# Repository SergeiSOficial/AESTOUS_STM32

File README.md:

# AiHi
Opensource thermostat for microbial bacteria incubator

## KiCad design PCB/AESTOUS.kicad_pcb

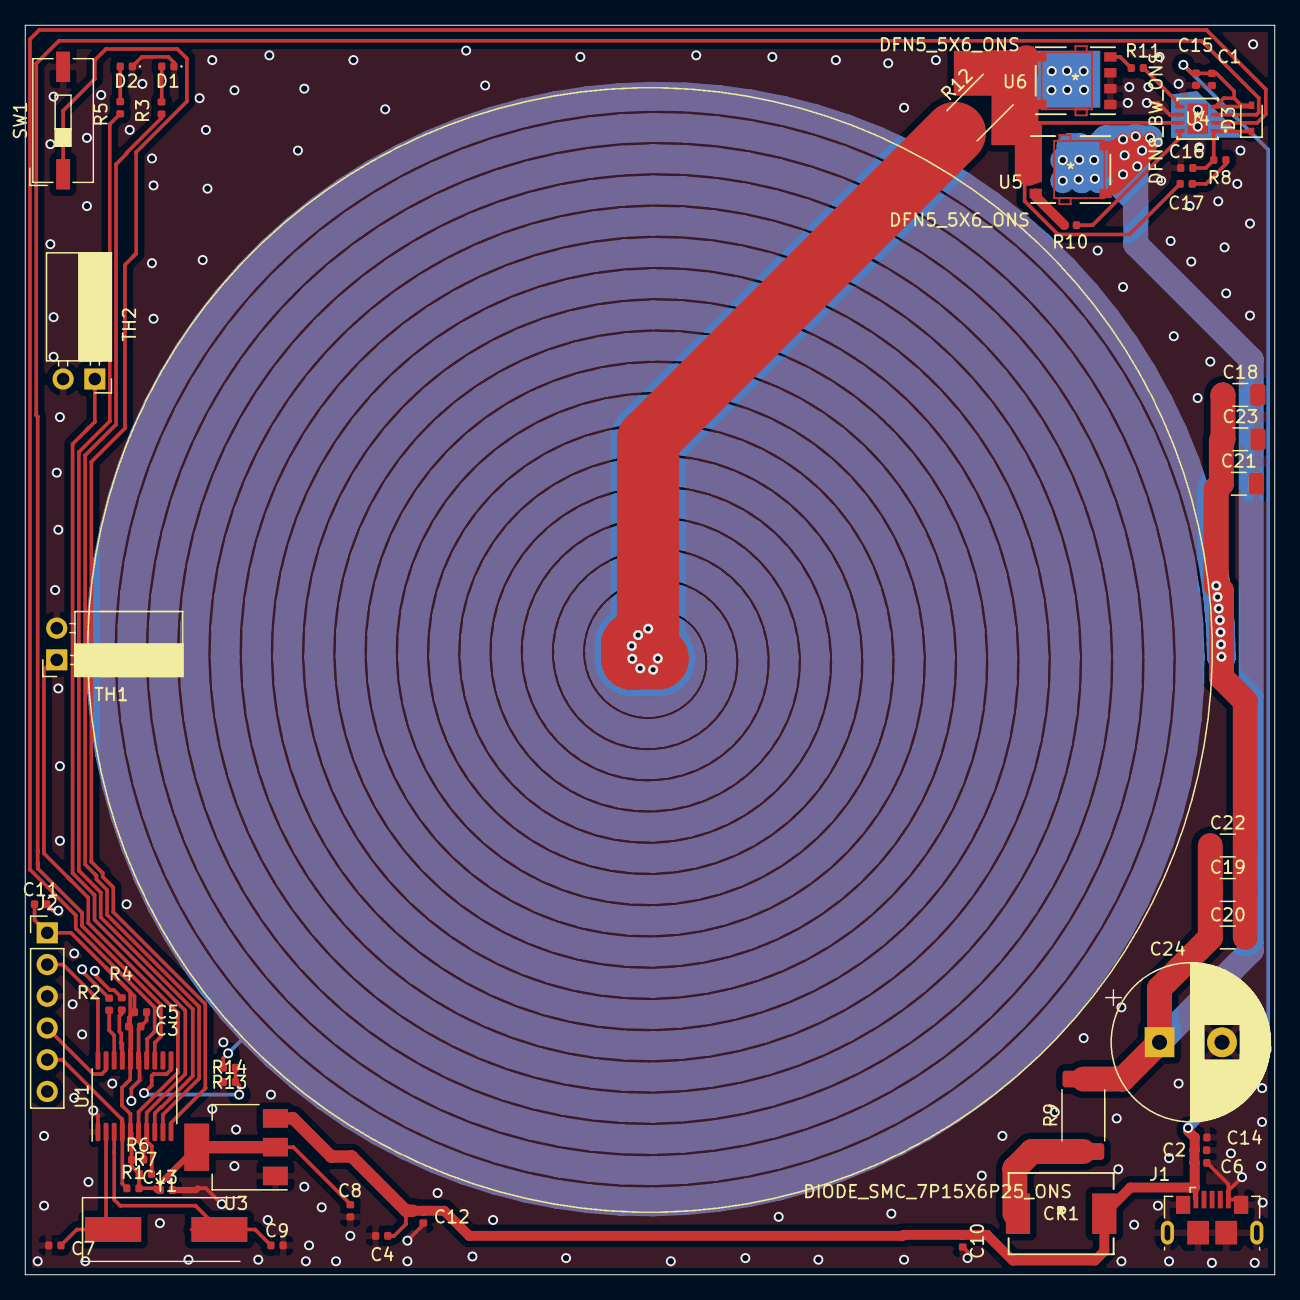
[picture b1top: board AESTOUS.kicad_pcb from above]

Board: 2 copper layers, 100.0 x 100.0 mm, 53 parts (0 on the bottom side), 32 nets.

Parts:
C1, C2, C3, C4, C5, C6, C8, C10, C11, C14: 1uf; C_0402_1005Metric
C7, C9: 12pf; C_0402_1005Metric
C12, C13, C15: 100pf; C_0402_1005Metric
C16, C17: 0.1uf; C_0402_1005Metric
C18, C19, C20, C21, C22, C23: 100uf; C_1206_3216Metric
C24: 4700uf; CP_Radial_D12.5mm_P5.00mm
CR1: DIODE_SMC_7P15X6P25_ONS; MBRS540T3G
D1, D2: LED; LED_0402_1005Metric
D3: BAS316; D_SOD-323
J1: USB_B_Micro; USB_Micro-B_GCT_USB3076-30-A
J2: Conn_01x06_Male; PinHeader_1x06_P2.54mm_Vertical
R1, R13, R14: 10k; R_0402_1005Metric
R2, R4: 33; R_0402_1005Metric
R3, R5: 330; R_0402_1005Metric
R6, R7: 5k; R_0402_1005Metric
R8: 2.2ohm; R_0402_1005Metric
R9: 0.1ohm; R_2512_6332Metric
R10, R11: 0ohm; R_0402_1005Metric
R12: 0.4ohm; R_2512_6332Metric
SW1: SW_Push; SW_DIP_SPSTx01_Slide_9.78x4.72mm_W8.61mm_P2.54mm
TH1, TH2: Thermistor_NTC; PinSocket_1x02_P2.54mm_Horizontal
U1: STM32F070F6Px; TSSOP-20_4.4x6.5mm_P0.65mm
U3: AP1117-33; SOT-223-3_TabPin2
U4: DFN8_BW_ONS; ADP3110AKCPZ-RL
U5, U6: DFN5_5X6_ONS; NTMFS4921NT1G
Y1: 8MHz; Crystal_SMD_HC49-SD

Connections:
0: C1.2, C2.2, C3.2, C4.2, C5.2, C6.2, C7.2, C8.2, C9.2, C10.2, C11.2, C12.2, C13.2, C14.2, C15.2, C16.1, C18.2, C21.2, C23.2, C24.2, D1.1, D2.1, J1.5, J1.6, J2.3, R14.1, SW1.2, TH1.2, TH2.2, U1.1, U1.15, U3.1, U4.6, U6.1, U6.2, U6.3
+3V3: C3.1, C5.1, C8.1, C11.1, C13.1, J2.1, R1.1, R6.1, R7.1, U1.5, U1.16, U3.2
+5V: C1.1, C2.1, C4.1, C6.1, C10.1, C12.1, C14.1, C15.1, CR1.2, D3.2, J1.1, U3.3, U4.4
/ADC_MIDDLE: R13.1, R14.2, U1.11
/NRST: J2.5, R1.2, U1.4
/Power/5v_Diode: C19.1, C20.1, C22.1, C24.1, R9.2, U5.5, U5.6
/Power/GATE_HI: R10.1, U4.8
/Power/GATE_LO: R11.1, U4.5
/Power/Heater1: C17.2, R12.2, U4.7, U5.1, U5.2, U5.3, U6.5, U6.6
/Power/Heater2: C18.1, C19.2, C20.2, C21.1, C22.2, C23.1, R12.1, R13.2
/SWCLK: J2.2, U1.20
/SWDIO: J2.4, U1.19
/TIM1_CH1N: U1.13, U4.3
/TIM1_CH3N: U1.14, U4.2
/USB_DM: R4.1, U1.17
/USB_DP: R2.1, U1.18
unnamed: C7.1, U1.2, Y1.1
unnamed: C9.1, U1.3, Y1.2
unnamed: C16.2, D3.1, R8.1, U4.1
unnamed: C17.1, R8.2
unnamed: CR1.1, R9.1
unnamed: D1.2, R3.1
unnamed: D2.2, R5.1
unnamed: J1.2, R2.2
unnamed: J1.3, R4.2
unnamed: R3.2, U1.9
unnamed: R5.2, U1.8
unnamed: R6.2, TH1.1, U1.6
unnamed: R7.2, TH2.1, U1.7
unnamed: R10.2, U5.4
unnamed: R11.2, U6.4
unnamed: SW1.1, U1.10

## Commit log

2020-07-25 First big commit
2020-07-25 Added ADC measurement
2020-07-25 Added pid regulator
2020-07-25 Added file for PID
2020-07-25 fix mypid include/ add tim generation
2020-07-25 Try to work with ADC
2020-07-25 simple test adc
2020-07-25 try to work with git
2020-07-25 Added RTC
2020-07-26 try to work with PID
2020-07-26 Added PCB
2020-07-26 Working PID/ need tune
2020-07-26 Added photo
2020-07-26 fix photo name

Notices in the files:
parts and their libraries:
Copyright 2016 Accelerated Designs. All rights reserved.
